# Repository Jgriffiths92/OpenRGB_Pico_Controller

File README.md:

# RGB Pico SATA Controller

This project is an open-source RGB controller designed to interface with 12v RGB devices using a Raspberry Pi Pico microcontroller. It features custom firmware and hardware, supporting the OpenRGB protocol for seamless integration with popular RGB control software.

RGB Pico SATA Controller is an open-source hardware and firmware project that enables control of standard (dumb) 12V RGB devices (such as common 12V RGB LED strips and PC lighting) using a Raspberry Pi Pico microcontroller. The controller connects via a SATA power connector for easy integration into PC builds and communicates with the OpenRGB desktop application using the OpenRGB protocol. This allows users to synchronize and customize their RGB lighting through a unified software interface.

The project includes:
- Custom PCB design (KiCad)
- Firmware written in C for the Raspberry Pi Pico
- Support for OpenRGB protocol for cross-platform compatibility

## Features
- Control standard (dumb) 12V RGB LEDs (common anode, 4-pin) via SATA power connector
- Seamless integration with OpenRGB software
- USB HID communication for low-latency control
- Open-source hardware (schematic, PCB, Gerber files)
- Easy-to-build firmware with CMake
- Designed for PC modding and custom lighting projects

## Folder Structure
- `Firmware/` — Source code for the Pico firmware (C, CMake)
- `Gerber/` — PCB manufacturing files for the controller
- `RGB_PICO_SATA_CONTROLLER.kicad_*` — KiCad schematic and PCB design files

## Hardware Overview
The hardware consists of a custom PCB designed in KiCad, featuring:
- Raspberry Pi Pico (RP2040) microcontroller
- SATA power input for 12V supply
- MOSFET drivers for switching 12V power to each RGB channel
- 4-pin connectors for standard 12V RGB LED strips (common anode)

All design files are provided in the repository (`.kicad_sch`, `.kicad_pcb`, and Gerber files).
## Getting Started
### Hardware
1. Open the KiCad project files (`RGB_PICO_SATA_CONTROLLER.kicad_sch`, `.kicad_pcb`) to view or modify the schematic and PCB layout.
2. Use the Gerber files in the `Gerber/` directory to order PCBs from your preferred manufacturer.
3. Assemble the board using the schematic and bill of materials (BOM).
4. Solder the Raspberry Pi Pico and connectors as indicated.

### Firmware
1. Install the Raspberry Pi Pico SDK and required toolchain (CMake, GCC, etc.).
2. Clone this repository and navigate to the `Firmware/` directory.
3. Build the firmware:
   ```sh
   mkdir build
   cd build
   cmake ..
   make
   ```
4. Connect your Pico in BOOTSEL mode and copy the generated `.uf2` file to the Pico's USB drive.

### Software (OpenRGB)
1. Download and install the OpenRGB application from [openrgb.org](https://openrgb.org/).
2. Connect the RGB Pico SATA Controller to your PC via USB.
3. Open OpenRGB and the controller should appear as a supported device.
4. Configure and control your RGB devices through the OpenRGB interface.

## OpenRGB Protocol
The firmware implements the OpenRGB protocol, allowing the controller to be recognized and managed by the OpenRGB desktop application. For protocol details, see `Firmware/openrgb_protocol.c` and `Firmware/openrgb_protocol.h`.

## License
## Contributing
Contributions are welcome! Please open issues or pull requests for bug fixes, new features, or suggestions.

## License
This project is licensed under the GNU General Public License v3.0 (GPLv3).

Copyright (C) [2026] [Your Name or Organization]

This program is free software: you can redistribute it and/or modify
it under the terms of the GNU General Public License as published by
the Free Software Foundation, either version 3 of the License, or
(at your option) any later version.

This program is distributed in the hope that it will be useful,
but WITHOUT ANY WARRANTY; without even the implied warranty of
MERCHANTABILITY or FITNESS FOR A PARTICULAR PURPOSE.  See the
GNU General Public License for more details.

You should have received a copy of the GNU General Public License
along with this program.  If not, see <https://www.gnu.org/licenses/>.

---
Feel free to contribute or open issues for suggestions and improvements.

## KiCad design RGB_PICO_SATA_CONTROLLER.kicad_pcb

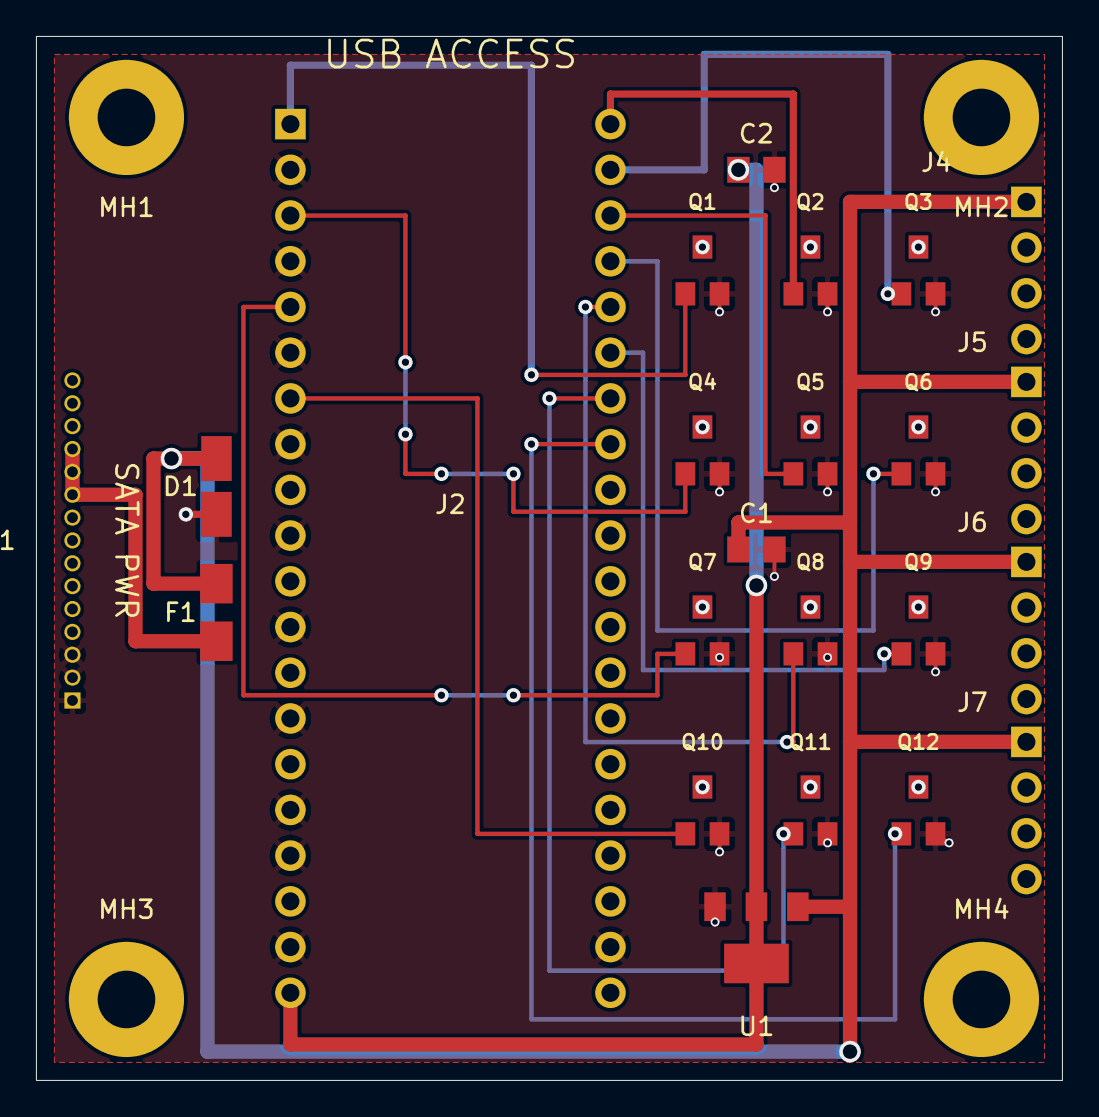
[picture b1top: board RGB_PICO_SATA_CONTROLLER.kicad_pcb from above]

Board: 4 copper layers, 57.0 x 58.0 mm, 27 parts (0 on the bottom side), 28 nets.

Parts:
C1, C2: 10uF; C_0805_2012Metric
D1: 1.5KE12A; D_SMB
F1: 1A; Fuse_1206_3216Metric
J1: SATA_POWER; PinHeader_1x15_P2.54mm_Vertical
J2: PICO_HEADER; PinHeader_2x20_P2.54mm_Vertical
J4: RGB1; PinHeader_1x04_P2.54mm_Vertical
J5: RGB2; PinHeader_1x04_P2.54mm_Vertical
J6: RGB3; PinHeader_1x04_P2.54mm_Vertical
J7: RGB4; PinHeader_1x04_P2.54mm_Vertical
MH1, MH2, MH3, MH4: MountingHole_3.2mm_M3
Q1, Q2, Q3, Q4, Q5, Q6, Q7, Q8, Q9, Q10, Q11, Q12: NMOS; SOT-23
U1: AMS1117-5.0; SOT-223-3_TabPin2

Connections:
+5V: C2.1, J2.39, U1.2, U1.4
+12V: F1.1, J1.10, J1.11, J1.12
+12V_F: C1.1, D1.2, F1.2, J4.1, J5.1, J6.1, J7.1, U1.3
GND: C1.2, C2.2, D1.1, J1.1, J1.2, J1.3, J2.3, J2.7, J2.11, J2.15, J2.19, J2.23, J2.27, J2.31, J2.33, J2.37, J2.38, Q1.2, Q2.2, Q3.2, Q4.2, Q5.2, Q6.2, Q7.2, Q8.2, Q9.2, Q10.2, Q11.2, Q12.2, U1.1
GP0: J2.1, Q1.1
GP1: J2.2, Q2.1
GP2: J2.4, Q3.1
GP3: J2.5, Q4.1
GP4: J2.6, Q5.1
GP5: J2.8, Q6.1
GP6: J2.9, Q7.1
GP7: J2.10, Q8.1
GP8: J2.12, Q9.1
GP9: J2.13, Q10.1
GP10: J2.14, Q11.1
GP11: J2.16, Q12.1
RGB1_B: J4.4, Q3.3
RGB1_G: J4.3, Q2.3
RGB1_R: J4.2, Q1.3
RGB2_B: J5.4, Q6.3
RGB2_G: J5.3, Q5.3
RGB2_R: J5.2, Q4.3
RGB3_B: J6.4, Q9.3
RGB3_G: J6.3, Q8.3
RGB3_R: J6.2, Q7.3
RGB4_B: J7.4, Q12.3
RGB4_G: J7.3, Q11.3
RGB4_R: J7.2, Q10.3

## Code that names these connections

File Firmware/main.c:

// Firmware for controlling standard (dumb) 12V RGB LED strips (common anode, 4-pin)
// Each color channel is controlled via PWM on a dedicated GPIO pin.
// Not for addressable LEDs (e.g., WS2812, SK6812).

#include "pico/stdlib.h"
#include "hardware/pwm.h"
#include "openrgb_protocol.h"


// Define GPIO pins for 4 RGB ports (change as needed for your board)
// Each port supports one standard 12V RGB LED strip (R, G, B channels)
#define RGB1_R 0
#define RGB1_G 1
#define RGB1_B 2
#define RGB2_R 3
#define RGB2_G 4
#define RGB2_B 5
#define RGB3_R 6
#define RGB3_G 7
#define RGB3_B 8
#define RGB4_R 9
#define RGB4_G 10
#define RGB4_B 11

void set_all_rgb(const uint8_t rgb[12]) {
    // Set PWM level for each color channel of each port
    // rgb[0..2]: Port 1 (R, G, B)
    // rgb[3..5]: Port 2 (R, G, B)
    // rgb[6..8]: Port 3 (R, G, B)
    // rgb[9..11]: Port 4 (R, G, B)
    pwm_set_gpio_level(RGB1_R, rgb[0] * 257);
    pwm_set_gpio_level(RGB1_G, rgb[1] * 257);
    pwm_set_gpio_level(RGB1_B, rgb[2] * 257);
    pwm_set_gpio_level(RGB2_R, rgb[3] * 257);
    pwm_set_gpio_level(RGB2_G, rgb[4] * 257);
    pwm_set_gpio_level(RGB2_B, rgb[5] * 257);
    pwm_set_gpio_level(RGB3_R, rgb[6] * 257);
    pwm_set_gpio_level(RGB3_G, rgb[7] * 257);
    pwm_set_gpio_level(RGB3_B, rgb[8] * 257);
    pwm_set_gpio_level(RGB4_R, rgb[9] * 257);
    pwm_set_gpio_level(RGB4_G, rgb[10] * 257);
    pwm_set_gpio_level(RGB4_B, rgb[11] * 257);
}

int main() {
    stdio_init_all();
    // Initialize PWM for all RGB pins (for dumb RGB strips)
    const uint RGB_PINS[12] = {
        RGB1_R, RGB1_G, RGB1_B,
        RGB2_R, RGB2_G, RGB2_B,
        RGB3_R, RGB3_G, RGB3_B,
        RGB4_R, RGB4_G, RGB4_B
    };
    for (int i = 0; i < 12; ++i) {
        gpio_set_function(RGB_PINS[i], GPIO_FUNC_PWM);
        uint slice = pwm_gpio_to_slice_num(RGB_PINS[i]);
        pwm_set_enabled(slice, true);
    }

    openrgb_init(set_all_rgb);
    while (1) {
        openrgb_task();
    }
    return 0;
}

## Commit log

2026-04-17 Initial commit: KiCad RGB SATA controller project
2026-04-17 Refactor code structure for improved readability and maintainability
2026-04-17 Add lock file to .gitignore to prevent tracking of temporary files
2026-04-17 Add temporary lock file for PCB to .gitignore
2026-04-17 Update .gitignore to include additional auto-saved files and prevent tracking
2026-04-19 Add backup zip file to .gitignore to prevent tracking
2026-04-19 Refactor RGB pin definitions and enhance firmware documentation in README.md
2026-04-19 Update .gitignore to exclude additional build files and modify CMakeLists.txt for SDK path configuration
2026-04-19 Update CMakeLists.txt to ensure minimum CMake version is set and add a comment for clarity
2026-04-19 Update .gitignore to exclude additional build files from the firmware build process
2026-04-19 Add CMake and VSCode configuration files for Raspberry Pi Pico support
2026-04-19 Add GPLv3 license file to the repository
2026-04-19 Add GPLv3 license information to README.md
